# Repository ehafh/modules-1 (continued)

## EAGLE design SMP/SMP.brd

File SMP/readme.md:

Overview
=======

Stereo Microsound Processor is a synthesizer module for the Buchla format, developed and manufactured by [1979](https://1979.ws/). It is based on [Clouds](https://mutable-instruments.net/modules/clouds/) by [Mutable Instruments](https://mutable-instruments.net/). The original source files for Clouds can be found in the [Mutable Instruments](https://github.com/pichenettes/eurorack) Github repository.

Visit [1979.ws/stereo-microsound-processor](https://1979.ws/stereo-microsound-processor/) for more information.

License
=======

These schematic and PCB files are distributed under the Creative Commons [CC-BY-SA 3.0](https://creativecommons.org/licenses/by-sa/3.0/) license, the same license used by the original hardware.

CC BY-SA 3.0 does not confer the right to use intellectual property such as trademarks, brand names, and logos. 1979, Stereo Microsound Processor, Mutable Instruments, and Clouds are trademarks of their respective owners and should not be used without permission.

Firmware
=======

Source code will be published soon.

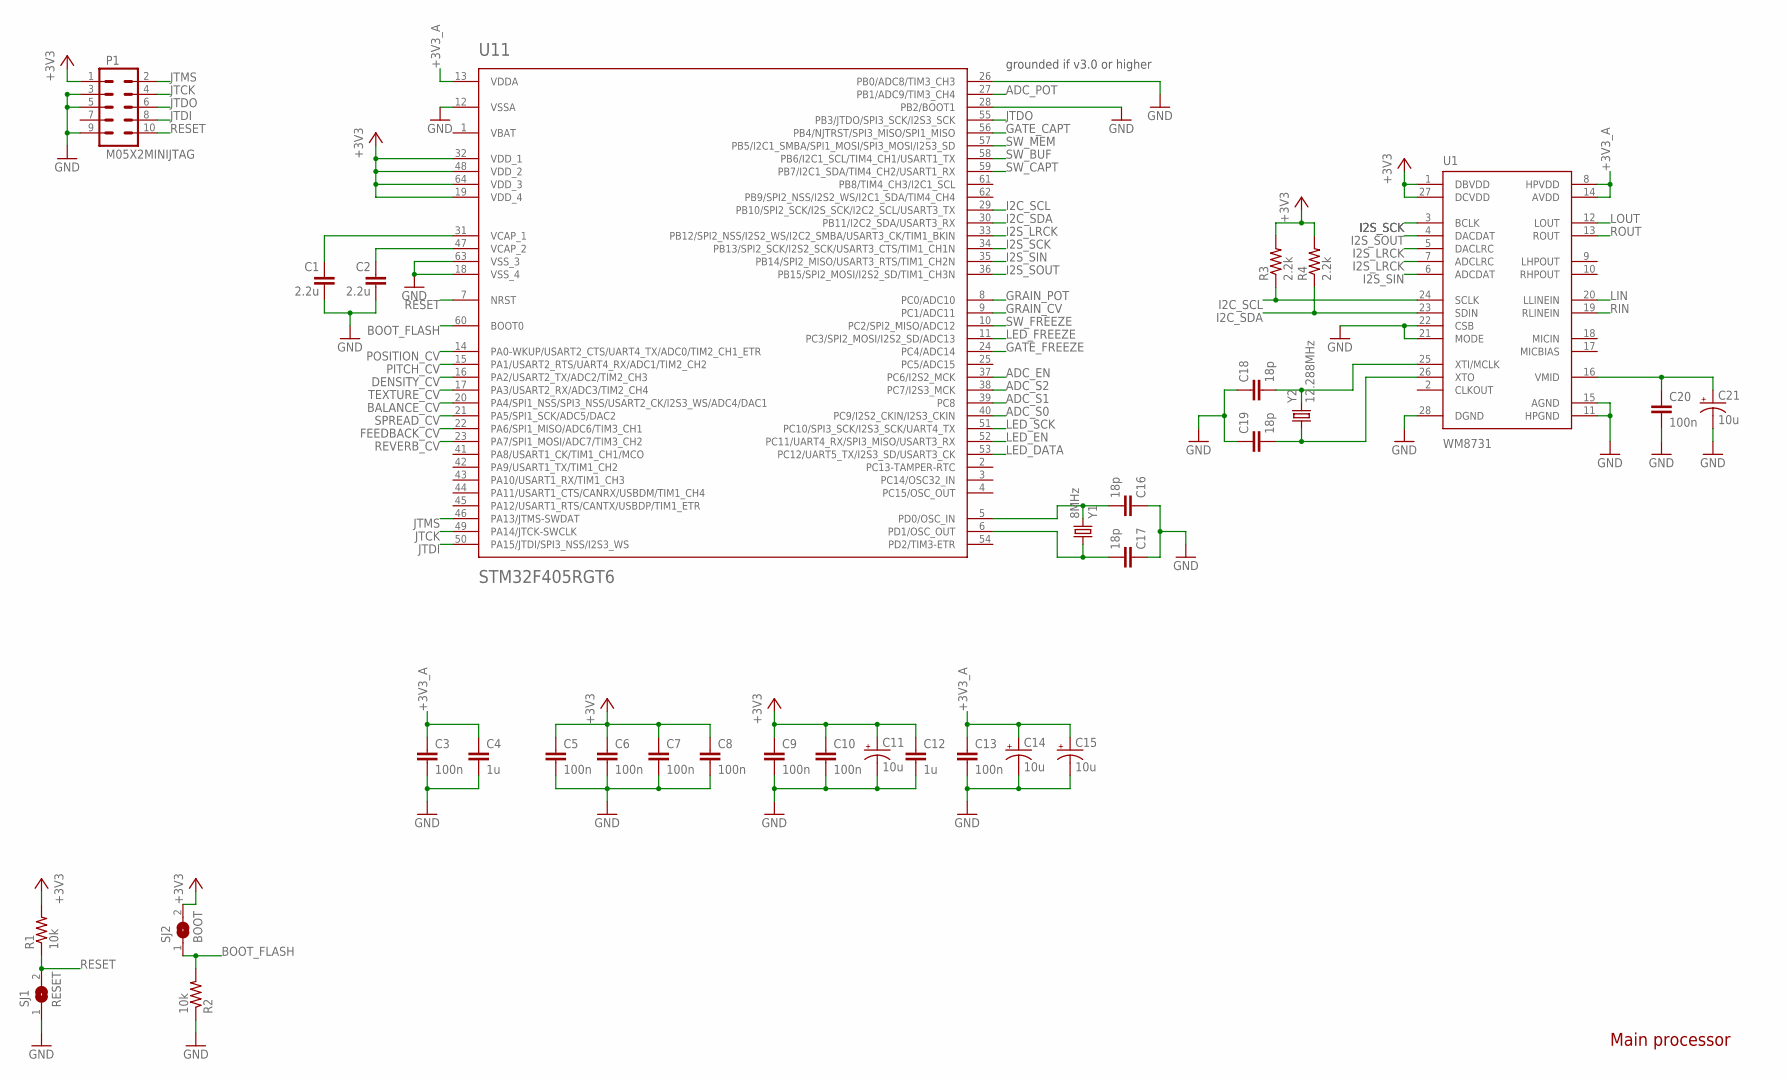
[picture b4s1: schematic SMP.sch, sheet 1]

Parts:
C1, C2: 2.2u; C0603
C3, C5, C6, C7, C8, C9, C10, C13, C20: 100n; C0603
C4, C12: 1u; C0603
C11, C14: 10u; PANASONIC_A
C15, C21: 10u; PANASONIC_B
C16, C17, C18, C19: 18p; C0603
P1: M05X2MINIJTAG; 2X5-1.27
R1, R2: 10k; R0603
R3, R4: 2.2k; R0603
SJ1: RESET; SJ
SJ2: BOOT; SJ
U1: WM8731; SSOP28
U11: STM32F405RGT6; TQFP-10X10-64
Y1: 8MHz; HC49UP
Y2: 12.288MHz; HC49UP

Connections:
+3V3: C5.1, C6.1, C7.1, C8.1, C9.1, C10.1, C11.+, C12.1, P1.1, R1.2, R3.2, R4.2, SJ2.2, U1.1 (DBVDD), U1.27 (DCVDD), U11.19 (VDD_4), U11.32 (VDD_1), U11.48 (VDD_2), U11.64 (VDD_3); also elsewhere on the board
+3V3_A: C3.1, C4.1, C13.1, C14.+, C15.+, U1.8 (HPVDD), U1.14 (AVDD), U11.13 (VDDA); also elsewhere on the board
ADC_EN: U11.37 (PC6/I2S2_MCK); also elsewhere on the board
ADC_POT: U11.27 (PB1/ADC9/TIM3_CH4); also elsewhere on the board
ADC_S0: U11.40 (PC9/I2S2_CKIN/I2S3_CKIN); also elsewhere on the board
ADC_S1: U11.39 (PC8); also elsewhere on the board
ADC_S2: U11.38 (PC7/I2S3_MCK); also elsewhere on the board
BALANCE_CV: U11.20 (PA4/SPI1_NSS/SPI3_NSS/USART2_CK/I2S3_WS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); also elsewhere on the board
BOOT_FLASH: R2.2, SJ2.1, U11.60 (BOOT0)
DENSITY_CV: U11.16 (PA2/USART2_TX/ADC2/TIM2_CH3); also elsewhere on the board
FEEDBACK_CV: U11.22 (PA6/SPI1_MISO/ADC6/TIM3_CH1); also elsewhere on the board
GATE_CAPT: U11.56 (PB4/NJTRST/SPI3_MISO/SPI1_MISO); also elsewhere on the board
GATE_FREEZE: U11.24 (PC4/ADC14); also elsewhere on the board
GND: C1.2, C2.2, C3.2, C4.2, C5.2, C6.2, C7.2, C8.2, C9.2, C10.2, C11.-, C12.2, C13.2, C14.-, C15.-, C16.1, C17.1, C18.1, C19.1, C20.2, C21.-, P1.3, P1.5, P1.9, R2.1, SJ1.1, U1.11 (HPGND), U1.15 (AGND), U1.21 (MODE), U1.22 (CSB), U1.28 (DGND), U11.12 (VSSA), U11.18 (VSS_4), U11.26 (PB0/ADC8/TIM3_CH3), U11.28 (PB2/BOOT1), U11.63 (VSS_3); also elsewhere on the board
GRAIN_CV: U11.9 (PC1/ADC11); also elsewhere on the board
GRAIN_POT: U11.8 (PC0/ADC10); also elsewhere on the board
I2C_SCL: R3.1, U1.24 (SCLK), U11.29 (PB10/SPI2_SCK/I2S_SCK/I2C2_SCL/USART3_TX)
I2C_SDA: R4.1, U1.23 (SDIN), U11.30 (PB11/I2C2_SDA/USART3_RX)
I2S_LRCK: U1.5 (DACLRC), U1.7 (ADCLRC), U11.33 (PB12/SPI2_NSS/I2S2_WS/I2C2_SMBA/USART3_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)
I2S_SCK: U1.3 (BCLK), U11.34 (PB13/SPI2_SCK/I2S2_SCK/USART3_CTS/TIM1_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)
I2S_SIN: U1.6 (ADCDAT), U11.35 (PB14/SPI2_MISO/USART3_RTS/TIM1_CH2N)
I2S_SOUT: U1.4 (DACDAT), U11.36 (PB15/SPI2_MOSI/I2S2_SD/TIM1_CH3N)
JTCK: P1.4, U11.49 (PA14/JTCK-SWCLK)
JTDI: P1.8, U11.50 (PA15/JTDI/SPI3_NSS/I2S3_WS)
JTDO: P1.6, U11.55 (PB3/JTDO/SPI3_SCK/I2S3_SCK)
JTMS: P1.2, U11.46 (PA13/JTMS-SWDAT)
LED_DATA: U11.53 (PC12/UART5_TX/I2S3_SD/USART3_CK); also elsewhere on the board
LED_EN: U11.52 (PC11/UART4_RX/SPI3_MISO/USART3_RX); also elsewhere on the board
LED_FREEZE: U11.11 (PC3/SPI2_MOSI/I2S2_SD/ADC13); also elsewhere on the board
LED_SCK: U11.51 (PC10/SPI3_SCK/I2S3_SCK/UART4_TX); also elsewhere on the board
LIN: U1.20 (LLINEIN); also elsewhere on the board
LOUT: U1.12 (LOUT); also elsewhere on the board
unnamed: C16.2, U11.5 (PD0/OSC_IN), Y1.2
unnamed: C17.2, U11.6 (PD1/OSC_OUT), Y1.1
unnamed: C2.1, U11.47 (VCAP_2)
unnamed: C20.1, C21.+, U1.16 (VMID)
unnamed: C1.1, U11.31 (VCAP_1)
unnamed: C19.2, U1.26 (XTO), Y2.1
unnamed: C18.2, U1.25 (XTI/MCLK), Y2.2
PITCH_CV: U11.15 (PA1/USART2_RTS/UART4_RX/ADC1/TIM2_CH2); also elsewhere on the board
POSITION_CV: U11.14 (PA0-WKUP/USART2_CTS/UART4_TX/ADC0/TIM2_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); also elsewhere on the board
RESET: P1.10, R1.1, SJ1.2, U11.7 (NRST)
REVERB_CV: U11.23 (PA7/SPI1_MOSI/ADC7/TIM3_CH2); also elsewhere on the board
RIN: U1.19 (RLINEIN); also elsewhere on the board
ROUT: U1.13 (ROUT); also elsewhere on the board
SPREAD_CV: U11.21 (PA5/SPI1_SCK/ADC5/DAC2); also elsewhere on the board
SW_BUF: U11.58 (PB6/I2C1_SCL/TIM4_CH1/USART1_TX); also elsewhere on the board
SW_CAPT: U11.59 (PB7/I2C1_SDA/TIM4_CH2/USART1_RX); also elsewhere on the board
SW_FREEZE: U11.10 (PC2/SPI2_MISO/ADC12); also elsewhere on the board
SW_MEM: U11.57 (PB5/I2C1_SMBA/SPI1_MOSI/SPI3_MOSI/I2S3_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); also elsewhere on the board
TEXTURE_CV: U11.17 (PA3/USART2_RX/ADC3/TIM2_CH4); also elsewhere on the board
VBAT: U11.1 (VBAT)

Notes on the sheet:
Main processor
grounded if v3.0 or higher

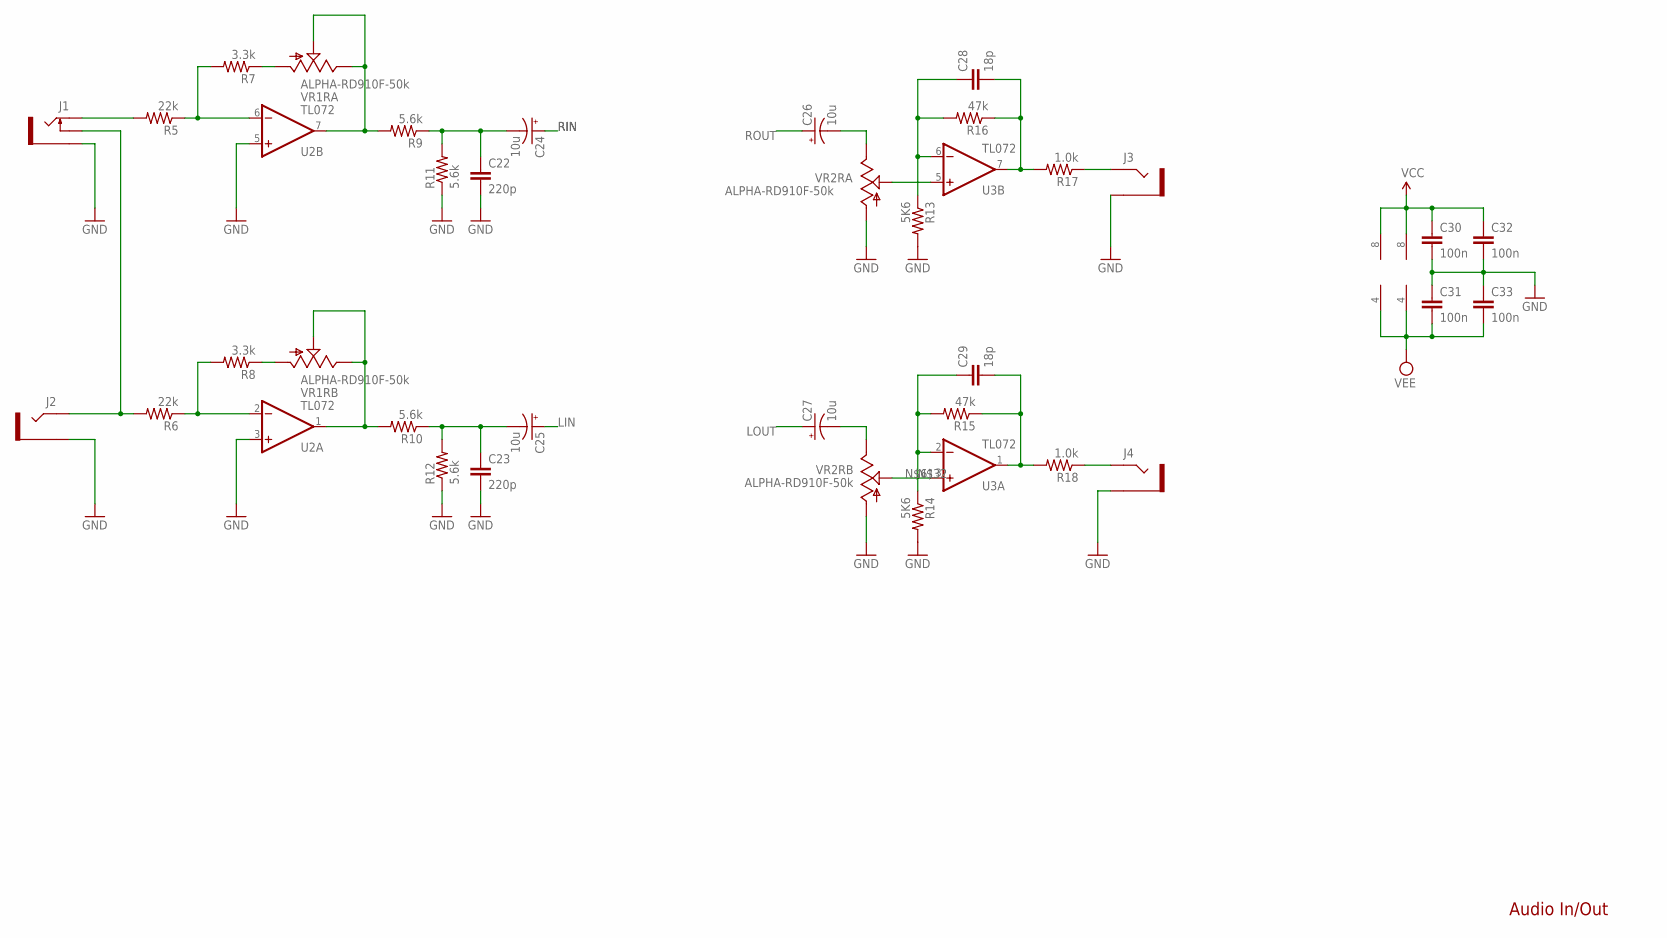
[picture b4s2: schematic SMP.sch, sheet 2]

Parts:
C22, C23: 220p; C0603
C24, C25, C26, C27: 10u; PANASONIC_B
C28, C29: 18p; C0603
C30, C31, C32, C33: 100n; C0603
J1: SWITCHCRAFT_42A; SWITCH_JOHNSON
J2, J3, J4: SWITCHCRAFT_JACK; SWITCH
R5, R6: 22k; R0603
R7, R8: 3.3k; R0603
R9, R10, R11, R12: 5.6k; R0603
R13, R14: 5K6; R0603
R15, R16: 47k; R0603
R17, R18: 1.0k; R0603
U2, U3: TL072; SO08
VR1, VR2: ALPHA-RD910F-50k; ALPHA902F

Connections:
GND: C22.2, C23.2, C30.2, C31.1, C32.2, C33.1, J1.G (1), J2.G (1), J3.G (1), J4.G (1), R11.1, R12.1, R13.2, R14.2, U2.3 (+IN), U2.5 (+IN), VR2.1R1 (1), VR2.1R2 (1); also elsewhere on the board
LIN: C25.+; also elsewhere on the board
LOUT: C27.+; also elsewhere on the board
LOUT_JACK: J4.S (2), R18.1
unnamed: C26.-, VR2.3R1 (3)
unnamed: C23.1, C25.-, R10.1, R12.2
unnamed: J1.S (3), R5.2
unnamed: J1.C (2), J2.S (2), R6.2
unnamed: C22.1, C24.-, R9.1, R11.2
unnamed: C27.-, VR2.3R2 (3)
unnamed: C28.1, R13.1, R16.2, U3.6 (-IN)
unnamed: C28.2, R16.1, R17.2, U3.7 (OUT)
unnamed: U3.5 (+IN), VR2.2R1 (2)
unnamed: C29.1, R14.1, R15.2, U3.2 (-IN)
unnamed: C29.2, R15.1, R18.2, U3.1 (OUT)
unnamed: R9.2, U2.7 (OUT), VR1.2R1 (2), VR1.3R1 (3)
unnamed: R10.2, U2.1 (OUT), VR1.2R2 (2), VR1.3R2 (3)
unnamed: R7.1, VR1.1R1 (1)
unnamed: R8.1, VR1.1R2 (1)
unnamed: R5.1, R7.2, U2.6 (-IN)
unnamed: R6.1, R8.2, U2.2 (-IN)
unnamed: U3.3 (+IN), VR2.2R2 (2)
RIN: C24.+; also elsewhere on the board
ROUT: C26.+; also elsewhere on the board
ROUT_JACK: J3.S (2), R17.1
VCC: C30.1, C32.1, U2.8 (V+), U3.8 (V+); also elsewhere on the board
VEE: C31.2, C33.2, U2.4 (V-), U3.4 (V-); also elsewhere on the board

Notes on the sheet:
Audio In/Out

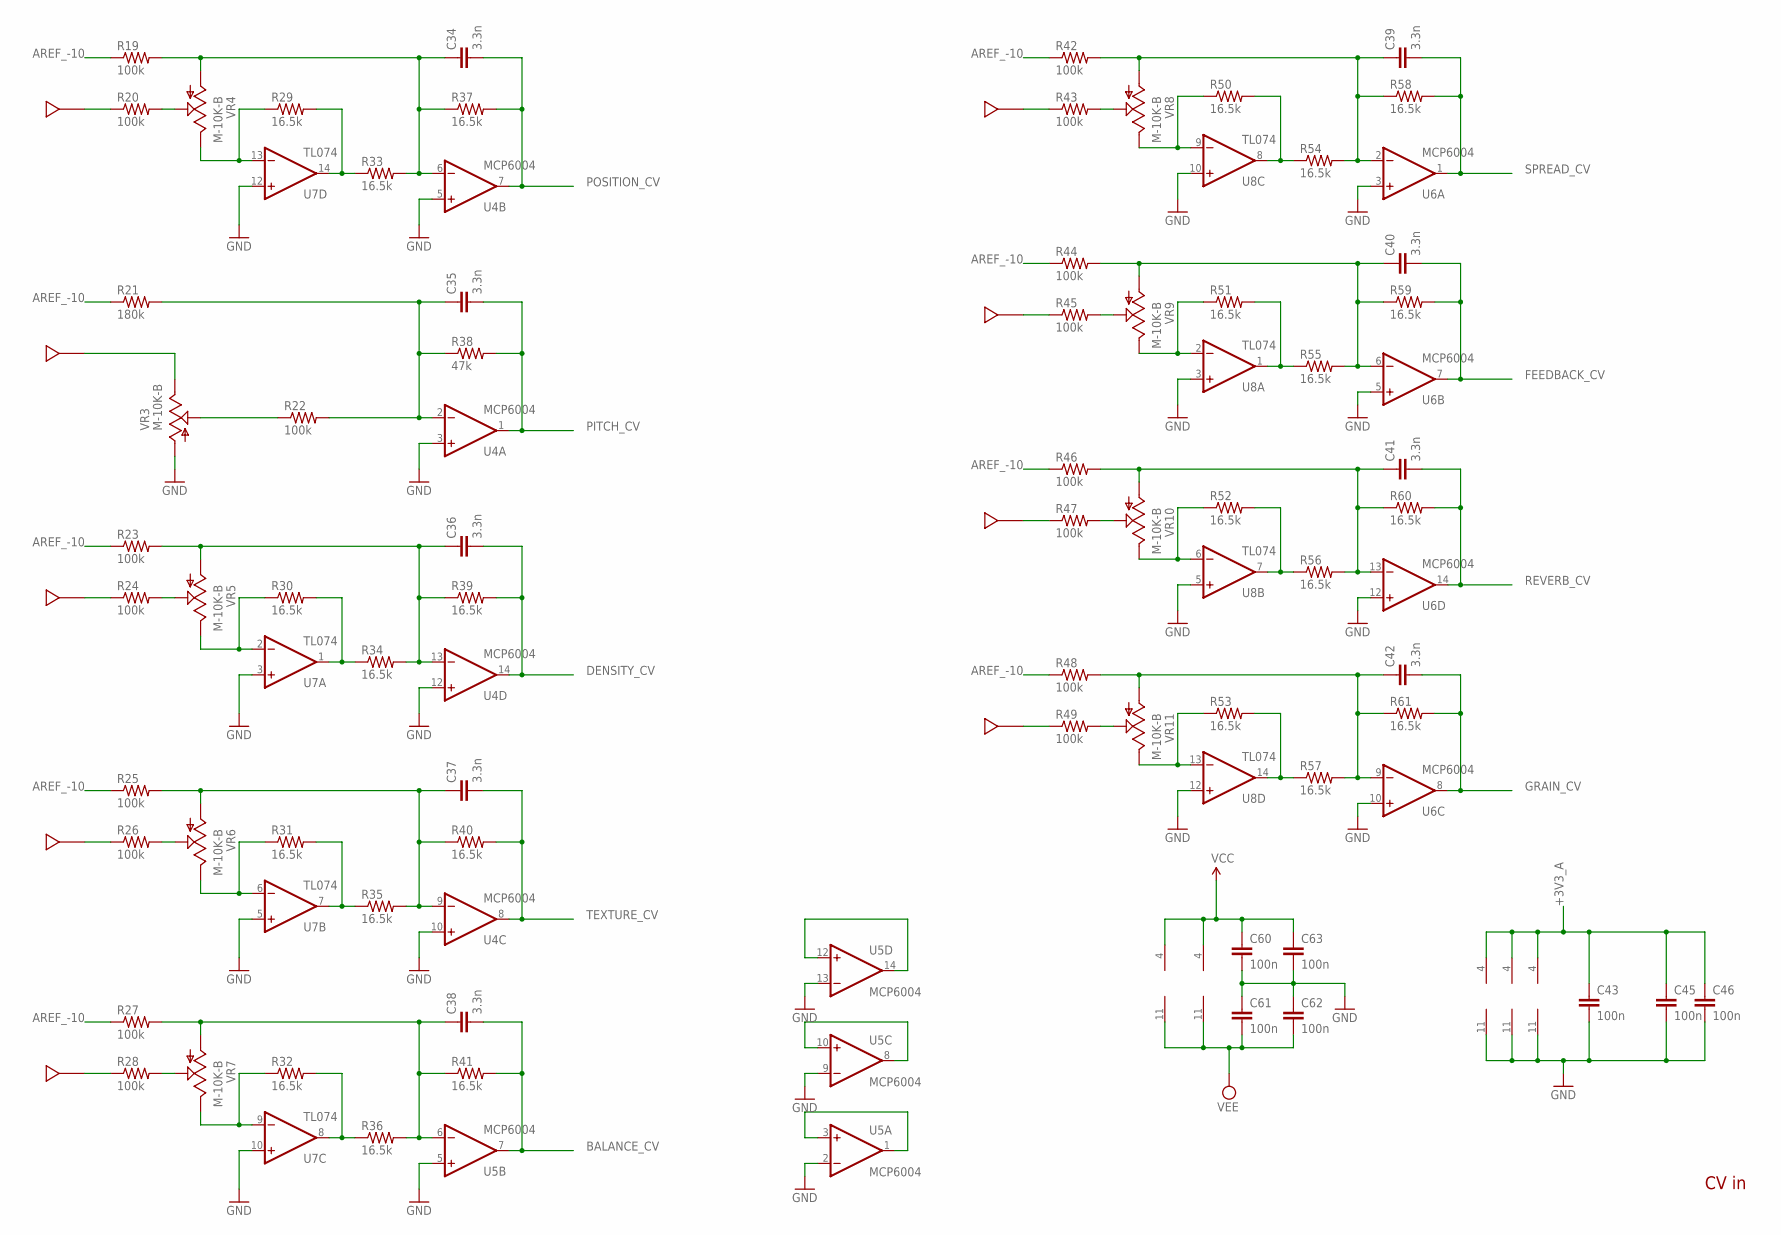
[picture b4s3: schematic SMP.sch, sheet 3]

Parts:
C34, C35, C36, C37, C38, C39, C40, C41, C42: 3.3n; C0603
C43, C45, C46, C60, C61, C62, C63: 100n; C0603
J5, J6, J7, J8, J9, J10, J11, J12, J13: JOHNSON_BANANASTD; JOHNSON
R19, R20, R22, R23, R24, R25, R26, R27, R28, R42, R43, R44, R45, R46, R47, R48, R49: 100k; R0603
R21: 180k; R0603
R29, R30, R31, R32, R33, R34, R35, R36, R37, R39, R40, R41, R50, R51, R52, R53, R54, R55, R56, R57, R58, R59, R60, R61: 16.5k; R0603
R38: 47k; R0603
U4, U5, U6: MCP6004; SO14
U7, U8: TL074; SO14
VR3, VR4, VR5, VR6, VR7, VR8, VR9, VR10, VR11: M-10K-B; ALPHA901F

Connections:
+3V3_A: C43.1, C45.1, C46.1, U4.4 (V+), U5.4 (V+), U6.4 (V+); also elsewhere on the board
AREF_-10: R19.1, R21.1, R23.1, R25.1, R27.1, R42.1, R44.1, R46.1, R48.1; also elsewhere on the board
BALANCE_CV: C38.2, R41.2, U5.7 (OUT); also elsewhere on the board
DENSITY_CV: C36.2, R39.2, U4.14 (OUT); also elsewhere on the board
FEEDBACK_CV: C40.2, R59.2, U6.7 (OUT); also elsewhere on the board
GND: C43.2, C45.2, C46.2, C60.2, C61.1, C62.1, C63.2, U4.3 (+IN), U4.5 (+IN), U4.10 (+IN), U4.11 (V-), U4.12 (+IN), U5.2 (-IN), U5.5 (+IN), U5.9 (-IN), U5.11 (V-), U5.13 (-IN), U6.3 (+IN), U6.5 (+IN), U6.10 (+IN), U6.11 (V-), U6.12 (+IN), U7.3 (+IN), U7.5 (+IN), U7.10 (+IN), U7.12 (+IN), U8.3 (+IN), U8.5 (+IN), U8.10 (+IN), U8.12 (+IN), VR3.1; also elsewhere on the board
GRAIN_CV: C42.2, R61.2, U6.8 (OUT); also elsewhere on the board
unnamed: J7.1, R24.1
unnamed: R43.2, VR8.2
unnamed: C36.1, R23.2, R34.2, R39.1, U4.13 (-IN), VR5.1
unnamed: R30.1, U7.2 (-IN), VR5.3
unnamed: R30.2, R34.1, U7.1 (OUT)
unnamed: J8.1, R26.1
unnamed: R47.2, VR10.2
unnamed: C37.1, R25.2, R35.2, R40.1, U4.9 (-IN), VR6.1
unnamed: R31.1, U7.6 (-IN), VR6.3
unnamed: R31.2, R35.1, U7.7 (OUT)
unnamed: J9.1, R28.1
unnamed: R49.2, VR11.2
unnamed: C38.1, R27.2, R36.2, R41.1, U5.6 (-IN), VR7.1
unnamed: R32.1, U7.9 (-IN), VR7.3
unnamed: J6.1, VR3.3
unnamed: R32.2, R36.1, U7.8 (OUT)
unnamed: J5.1, R20.1
unnamed: J10.1, R43.1
unnamed: R28.2, VR7.2
unnamed: U5.12 (+IN), U5.14 (OUT)
unnamed: C34.1, R19.2, R33.2, R37.1, U4.6 (-IN), VR4.1
unnamed: R22.1, VR3.2
unnamed: R29.1, U7.13 (-IN), VR4.3
unnamed: R29.2, R33.1, U7.14 (OUT)
unnamed: R26.2, VR6.2
unnamed: C35.1, R21.2, R22.2, R38.1, U4.2 (-IN)
unnamed: J11.1, R45.1
unnamed: R24.2, VR5.2
unnamed: C39.1, R42.2, R54.2, R58.1, U6.2 (-IN), VR8.1
unnamed: R50.1, U8.9 (-IN), VR8.3
unnamed: R50.2, R54.1, U8.8 (OUT)
unnamed: J12.1, R47.1
unnamed: R45.2, VR9.2
unnamed: C40.1, R44.2, R55.2, R59.1, U6.6 (-IN), VR9.1
unnamed: R51.1, U8.2 (-IN), VR9.3
unnamed: R51.2, R55.1, U8.1 (OUT)
unnamed: U5.8 (OUT), U5.10 (+IN)
unnamed: C41.1, R46.2, R56.2, R60.1, U6.13 (-IN), VR10.1
unnamed: R52.1, U8.6 (-IN), VR10.3
unnamed: R52.2, R56.1, U8.7 (OUT)
unnamed: J13.1, R49.1
unnamed: R20.2, VR4.2
unnamed: C42.1, R48.2, R57.2, R61.1, U6.9 (-IN), VR11.1
unnamed: R53.1, U8.13 (-IN), VR11.3
unnamed: R53.2, R57.1, U8.14 (OUT)
unnamed: U5.1 (OUT), U5.3 (+IN)
PITCH_CV: C35.2, R38.2, U4.1 (OUT); also elsewhere on the board
POSITION_CV: C34.2, R37.2, U4.7 (OUT); also elsewhere on the board
REVERB_CV: C41.2, R60.2, U6.14 (OUT); also elsewhere on the board
SPREAD_CV: C39.2, R58.2, U6.1 (OUT); also elsewhere on the board
TEXTURE_CV: C37.2, R40.2, U4.8 (OUT); also elsewhere on the board
VCC: C60.1, C63.1, U7.4 (V+), U8.4 (V+); also elsewhere on the board
VEE: C61.2, C62.2, U7.11 (V-), U8.11 (V-); also elsewhere on the board

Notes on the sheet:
CV in

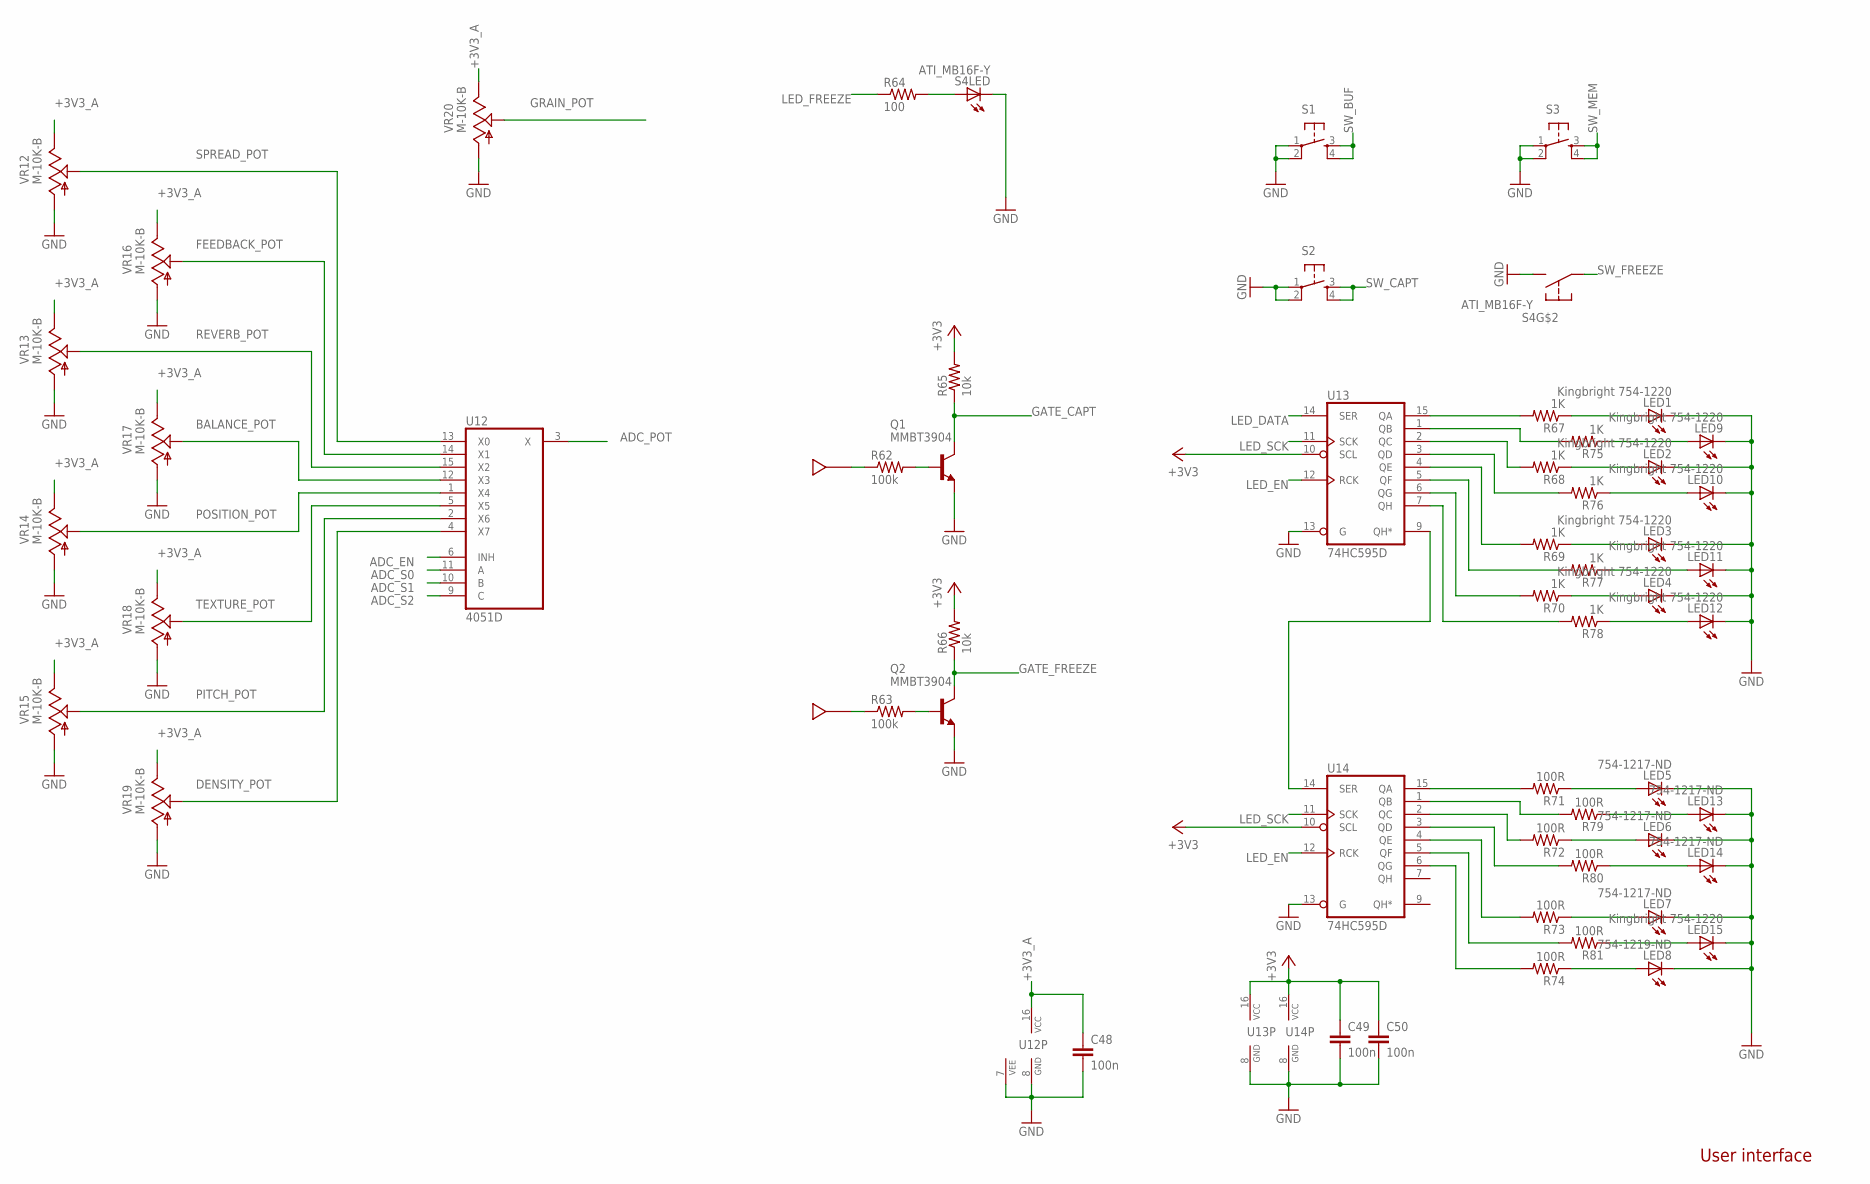
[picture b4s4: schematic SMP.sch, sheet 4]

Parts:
C48, C49, C50: 100n; C0603
J14, J15: JOHNSON_BANANASTD; JOHNSON
LED1, LED2, LED3, LED4, LED9, LED10, LED11, LED12, LED15: Kingbright 754-1220; LED_3MM_MIN
LED5, LED6, LED7, LED13, LED14: 754-1217-ND; LED_3MM_MIN
LED8: 754-1219-ND; LED_3MM_MIN
Q1, Q2: MMBT3904; SOT23-BEC
R62, R63: 100k; R0603
R64: 100; R0603
R65, R66: 10k; R0603
R67, R68, R69, R70, R75, R76, R77, R78: 1K; R0603
R71, R72, R73, R74, R79, R80, R81: 100R; R0603
S1, S2, S3: TAC_SWITCH; C&K_D6R
S4: ATI_MB16F-Y; MB16F
U12: 4051D; SO16
U13, U14: 74HC595D; SO16
VR12, VR13, VR14, VR15, VR16, VR17, VR18, VR19, VR20: M-10K-B; ALPHA901F

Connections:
+3V3: C49.1, C50.1, R65.2, R66.2, U13.10 (SCL), U13.16 (VCC), U14.10 (SCL), U14.16 (VCC); also elsewhere on the board
+3V3_A: C48.1, U12.16 (VCC), VR12.3, VR13.3, VR14.3, VR15.3, VR16.3, VR17.3, VR18.3, VR19.3, VR20.3; also elsewhere on the board
ADC_EN: U12.6 (INH); also elsewhere on the board
ADC_POT: U12.3 (X); also elsewhere on the board
ADC_S0: U12.11 (A); also elsewhere on the board
ADC_S1: U12.10 (B); also elsewhere on the board
ADC_S2: U12.9 (C); also elsewhere on the board
BALANCE_POT: U12.12 (X3), VR17.2
DENSITY_POT: U12.4 (X7), VR19.2
FEEDBACK_POT: U12.14 (X1), VR16.2
GATE_CAPT: Q1.C, R65.1; also elsewhere on the board
GATE_FREEZE: Q2.C, R66.1; also elsewhere on the board
GND: C48.2, C49.2, C50.2, LED1.K (C), LED2.K (C), LED3.K (C), LED4.K (C), LED5.K (C), LED6.K (C), LED7.K (C), LED8.K (C), LED9.K (C), LED10.K (C), LED11.K (C), LED12.K (C), LED13.K (C), LED14.K (C), LED15.K (C), Q1.E, Q2.E, S1.1, S1.2, S2.1, S2.2, S3.1, S3.2, S4.1 (2), S4.4 (L2), U12.7 (VEE), U12.8 (GND), U13.8 (GND), U13.13 (G), U14.8 (GND), U14.13 (G), VR12.1, VR13.1, VR14.1, VR15.1, VR16.1, VR17.1, VR18.1, VR19.1, VR20.1; also elsewhere on the board
GRAIN_POT: VR20.2; also elsewhere on the board
LED_DATA: U13.14 (SER); also elsewhere on the board
LED_EN: U13.12 (RCK), U14.12 (RCK); also elsewhere on the board
LED_FREEZE: R64.1; also elsewhere on the board
LED_SCK: U13.11 (SCK), U14.11 (SCK); also elsewhere on the board
unnamed: LED9.A, R75.1
unnamed: LED1.A, R67.1
unnamed: LED2.A, R68.1
unnamed: LED10.A, R76.1
unnamed: LED3.A, R69.1
unnamed: J15.1, R63.1
unnamed: Q2.B, R63.2
unnamed: R64.2, S4.3 (L1)
unnamed: LED11.A, R77.1
unnamed: LED4.A, R70.1
unnamed: LED12.A, R78.1
unnamed: R67.2, U13.15 (QA)
unnamed: R75.2, U13.1 (QB)
unnamed: R68.2, U13.2 (QC)
unnamed: R76.2, U13.3 (QD)
unnamed: R69.2, U13.4 (QE)
unnamed: R77.2, U13.5 (QF)
unnamed: R70.2, U13.6 (QG)
unnamed: R78.2, U13.7 (QH)
unnamed: J14.1, R62.1
unnamed: LED13.A, R79.1
unnamed: Q1.B, R62.2
unnamed: LED5.A, R71.1
unnamed: LED6.A, R72.1
unnamed: LED14.A, R80.1
unnamed: LED7.A, R73.1
unnamed: LED15.A, R81.1
unnamed: LED8.A, R74.1
unnamed: R71.2, U14.15 (QA)
unnamed: R79.2, U14.1 (QB)
unnamed: R72.2, U14.2 (QC)
unnamed: R80.2, U14.3 (QD)
unnamed: R73.2, U14.4 (QE)
unnamed: R81.2, U14.5 (QF)
unnamed: R74.2, U14.6 (QG)
unnamed: U13.9 (QH*), U14.14 (SER)
PITCH_POT: U12.2 (X6), VR15.2
POSITION_POT: U12.1 (X4), VR14.2
REVERB_POT: U12.15 (X2), VR13.2
SPREAD_POT: U12.13 (X0), VR12.2
SW_BUF: S1.3, S1.4; also elsewhere on the board
SW_CAPT: S2.3, S2.4; also elsewhere on the board
SW_FREEZE: S4.2 (1); also elsewhere on the board
SW_MEM: S3.3, S3.4; also elsewhere on the board
TEXTURE_POT: U12.5 (X5), VR18.2

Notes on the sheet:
User interface

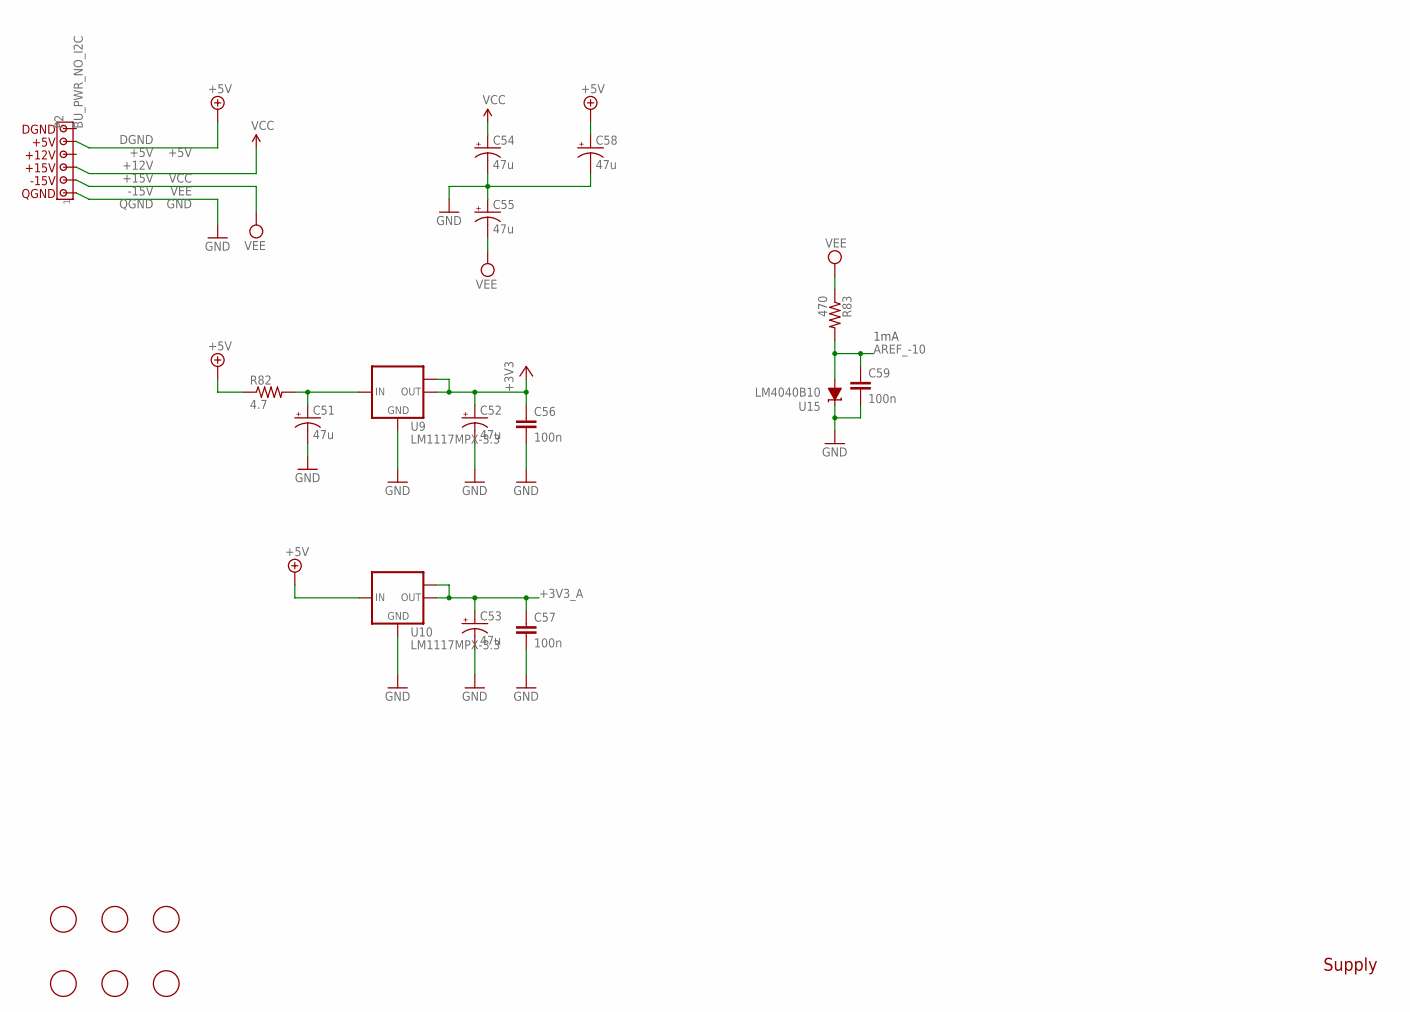
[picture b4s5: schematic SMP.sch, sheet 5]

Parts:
C51, C52, C53, C54, C55, C58: 47u; PANASONIC_D
C56, C57, C59: 100n; C0603
FD1, FD2, FD3, FD4, FD5, FD6: FIDUCIAL; FIDUCIAL_1MM
P2: BU_PWR_NO_I2C; MTA_156
R82: 4.7; R1206
R83: 470; R0603
U9, U10: LM1117MPX-3.3; SOT223
U15: LM4040B10; DBZ_R-PDSO-G3

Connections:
+3V3: C52.+, C56.1, U9.2 (OUT), U9.TAB (OUT1); also elsewhere on the board
+3V3_A: C53.+, C57.1, U10.2 (OUT), U10.TAB (OUT1); also elsewhere on the board
+5V: C58.+, P2.5, R82.1, U10.3 (IN)
AREF_-10: C59.1, R83.2, U15.2 (A); also elsewhere on the board
GND: C51.-, C52.-, C53.-, C54.-, C55.+, C56.2, C57.2, C58.-, C59.2, P2.1, U9.1 (GND), U10.1 (GND), U15.1 (C); also elsewhere on the board
unnamed: C51.+, R82.2, U9.3 (IN)
VCC: C54.+, P2.3; also elsewhere on the board
VEE: C55.-, P2.2, R83.1; also elsewhere on the board

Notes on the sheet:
1mA
Supply
QGND
-15V
+15V
+12V
+5V
DGND

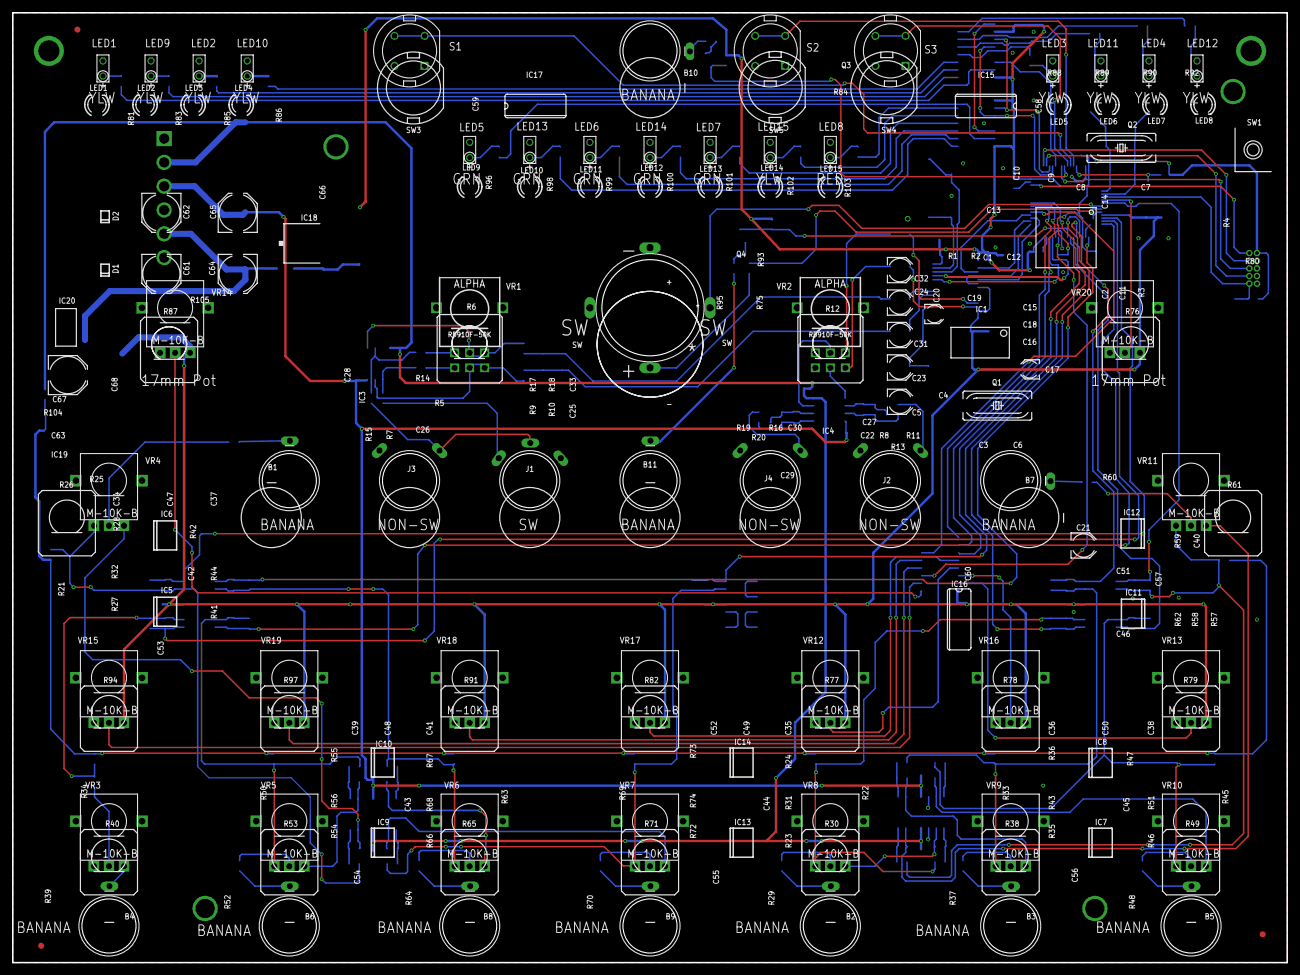
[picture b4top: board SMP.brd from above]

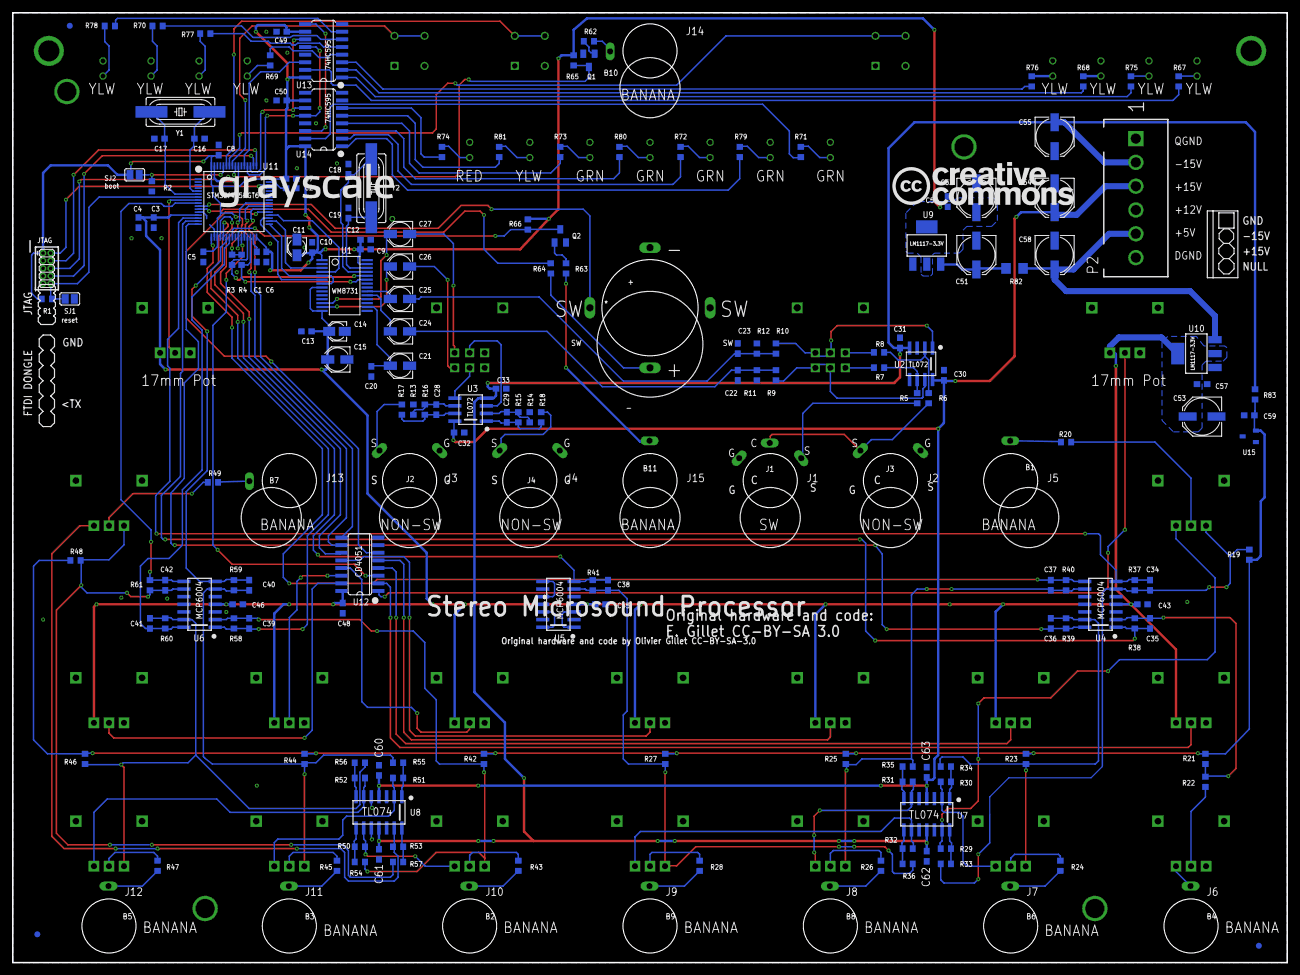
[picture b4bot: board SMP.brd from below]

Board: 2 copper layers, 212.0 x 158.0 mm, 227 parts (170 on the bottom side), 166 nets.

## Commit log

2020-10-25 Adding SMP firmware
